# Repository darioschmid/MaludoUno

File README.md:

# MaludoUno

How to make the Maludo Uno, a single key Digispark Morse Code Keyboard mainly intended as a keychain suitable gadget.\
It runs my [Digispark Morse Keyboard](https://github.com/darioschmid/DigisparkMorseKeyboard) Arduino script.

## Inspiration

I was inspired by [Snipeye's Uno](https://www.reddit.com/r/mechmarket/comments/h8b27d/gb_uno_last_chance/):

It's based on the AtMega32u4 Microcontroller. In contrast, my "Maludo Uno" is based on the weaker, but cheaper AtTiny85/Digispark.

## My "Maludo Uno" Design

I used my [Digispark Morse Keyboard](https://github.com/darioschmid/DigisparkMorseKeyboard) Arduino Script to be able to use Morse Code for Input. Previously I hardly knew any Morse Codes, but I reckoned this would be quite a fun project for getting involved into Morse Code.

### Advantages

* More cost efficient: 5 Digispark Boards are about 10€ on [Banggood](https://www.banggood.com/5Pcs-Digispark-Kickstarter-Micro-USB-Development-Board-For-ATTINY85-Arduino-p-1047665.html?rmmds=search&cur_warehouse=CN) and [Amazon](https://www.amazon.de/AZDelivery-Digispark-kompatibles-Development-ATtiny85/dp/B076KVKHH1) (incl. shipping), whereas a single AtMega32u4 board is at least 5€
* Speed Switch for adjusting the Morse Code timings
* Smaller

### Disadvantages

* No support for a RGB LED (too little available pins on the Digispark)
* Not QMK support (but full Arduino IDE support)

## How To Use It

Visit [DigisparkMorseCode/MorseCodes.txt](https://raw.githubusercontent.com/darioschmid/DigisparkMorseKeyboard/master/MorseCodes.txt), or open a Text Editor and hold the key down for 4sec. It prints out all available Morse Codes. Hold down the key to switch between DE and US keyboard layout.

Example:

    "M  A   L    U   D   O      U  N   O"
    "-- •- •-•• ••- -•• ---    ••- -• ---"

Setting the Speed Switch to "Fast" activates automatic space insertion between words and allows your "dah's" (long presses) to be shorter.\
If you set the switch to "Slow", you must manually add spaces between words with the morse codes "----" or "•-•••".

## How To Do It Yourself

1. Get a [Digispark](https://www.amazon.de/AZDelivery-Digispark-kompatibles-Development-ATtiny85/dp/B076KVKHH1)
2. Order the PCB (I got mine from [jlcpcb.com](https://jlcpcb.com/)). You can find the gerber files at [./KiCadFiles/GerberFiles](https://github.com/darioschmid/MaludoUno/tree/master/KiCadFiles)
3. Get yourself a Cherry MX style key switch
4. (Optional) Get yourself a [MSK 12C01](https://www.ebay.de/itm/SMD-Miniatur-Schiebeschalter-Switch-Schalter-Micro-Mini-Ein-Aus-3-Pin-MSK-12C01/173613966570) SMD Switch
5. [Assembly](https://github.com/darioschmid/MaludoUno/tree/master/Soldering)
   1. Solder Male Headers onto the Digispark (facing upwards)
   2. Solder the Speed Switch onto the PCB. This requires precise SMD soldering as the switch is tiny
   3. Solder the key switch onto the PCB
   4. Solder the PCB to the Digispark
6. Upload the code to the Digispark. Visit my [DigisparkMorseKeyboard repository](https://github.com/darioschmid/DigisparkMorseKeyboard) for reference.

Feel free to improve my PCB design (e.g. add compability for other key switches). You can find the KiCad PCB Design files at [./KiCadFiles](https://github.com/darioschmid/MaludoUno/tree/master/KiCadFiles).

The PCB inside KiCad looks like this:

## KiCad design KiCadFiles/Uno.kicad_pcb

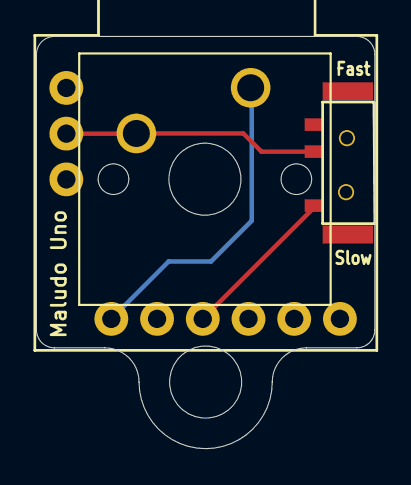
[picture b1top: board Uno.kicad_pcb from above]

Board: 2 copper layers, 18.8 x 22.9 mm, 3 parts (0 on the bottom side), 3 nets.

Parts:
Maludo Uno: KEYSW; SW_Cherry_MX_1.00u_PCB
SW1: SW_Push; MSK12C02
U1: Digispark

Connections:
GND: Maludo Uno.2, SW1.2, U1.8
unnamed: Maludo Uno.1, U1.1
unnamed: SW1.1, U1.3

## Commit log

2020-09-26 ehre
2020-09-26 updated Amazon prices
2020-10-30 Linked Soldering Tutorial
2020-10-30 Refined Soledering Instructions
2023-01-05 refactored urls
